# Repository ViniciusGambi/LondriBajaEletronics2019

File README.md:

# LondriBajaEletronics2019

> Este repositório conta um pouco a jornada da evolução do subsistema de elétrica da equipe LondriBaja entre novembro de 2018 e março de 2020. Os detalhes de implementação de cada uma das partes do projeto citadas estão sendo adicionadas em repositórios individuais, as quais seus links são citados aqui ao longo desse texto.

## Jornada

Em Agosto de 2018, novatos na equipe, que naquele momento estava sem membros no subsistema de elétrica, topamos o desafio de mesmo sem estar cursando graduação nas áreas afins, estudar o necessário para conseguir levar um sistema de segurança robusto para a competição, que não gerasse alto número de rechecks para a equipe. A competição Regional Sul seria em outubro. Trabalhamos duro aqueles dois meses para isso. Conseguimos finalizar alguns dias antes da competição, e observando as necessidades da equipe para aquele momento, projetamos um simples sistema para aferir níveis baixos de combustível, de fabricação manual, bem simples, mas que funcionava. Conseguimos chegar na competição e o resultado foi 0 rechecks, e conseguimos uma boa nota, embora marinheiros de primeira viagem. O feedback dos juízes e experiências trocadas com as demais equipes nos mostravam que o segredo era começar com pouco, mas fazer bem feito. Isso nos deu ânimo e mostrava que estávamos no caminho certo. 

Iniciamos então uma nova fase. Definimos então algumas metas. O prazo final era a competição Nacional em março de 2020. Colheríamos mais feedbacks dos juízes nas competições Nacional de 2019, em fevereiro, e Regional Sul de novembro de 2020.

- Implementar o primeiro sistema de instrumentação desenvolvido pela equipe
- Otimizar a proteção contra líquidos do então atual sistema de segurança da equipe
- Desenvolver um sensor de baixo custo para aferir o deslocamento da suspensão
- Desenvolver um aplicativo que facilitasse o processo de fazer inspeções de segurança

### A instalação elétrica

Toda a instalação elétrica do veículo foi novamente projetada em busca de reduzir a massa total do sistema, torná-la mais robusta e mais resistente a líquidos, e mais modular em busca de acelerar o processo de manutenção. O chicote foi fabricado  com tubo anti chamas, conectores IP66, prensa-cabos.Foram projetadas caixas vedadas, fabricadas com impressão 3d e borrachas para a proteção contra líquidos dos botões de emergência.

### Sensoriamento

Seguindo o princípio de fazer algo enxuto, simples porém bem feito, para essa primeira versão foi optado por aferir 3 grandezas: RPM do motor, velocidade do veículo e nível de combustível. Os métodos escolhido para RPM foi extrair os pulsos gerados na bobina da vela, para a velocidade foi o posicionamento de um sensor indutivo no eixo da roda para contagem de pulsos, e para o combustível posicionar sensores capacitivos digitais externos ao tanque (visto que a competição proíbe utilizar sensores dentro do tanque). Mais detalhes podem ser vistos nos repositórios individuais (a serem criados).

### Projeto Elétrico e Eletrônico

O diagrama abaixo mostra como ficou organizado o sistema de segurança junto ao sistema eletrônico. 

O sistema eletrônico foi dividido em duas PCB’s, uma ECU, principal, que cuida do do controle das tensões, conecta o microcontrolador, que trabalha os dados, as entradas dos sensores, e expõe os dados para a Serial e outra PCB, que é um display com leds e displays de 7 segmentos que é utilizada como painel. 
O controle das tensões é feito por dois reguladores buck por apresentarem eficiências mais altas. O microcontrolador, um ATMega328p, foi escolhido para garantir o andamento do projeto no futuro da equipe. Como em nossa universidade não temos alunos cursando a área de eletrônica e afins, essa escolha facilita para que o projeto não fique estagnado até que futuros novos membros possam aprender a programar microcontroladores de baixo nível, pelo fato desse microcontrolador poder ser programado com a biblioteca Arduino, que tem uma grande comunidade e é de fácil aprendizagem. E mesmo assim, se adequa aos requisitos do projeto, atendendo as necessidades do projeto. Os esquemáticos e detalhes da implementação podem ser extraídos nos repositório X.

Foram projetadas caixas vedadas, como as do sistema de segurança, para o sistema de instrumentação. Foram desenvolvidas duas versões das caixas de proteção nesse tempo. A primeira foi projetada em forma de gaveta, em busca de fácil manutenção caso necessário, e guardava ambas as duas PCBs. É a implementada no veículo ao fim deste projeto. A segunda versão separa as PCB’s em duas caixas, em busca de maior modularidade, e substitui os conectores que são utilizadas na primeira versão, por sensores automotivos que se conectam diretamente a PCB, para tornar a solução mais automotiva, e retirar os prensa-cabos. Essa versão será fabricada em 2020, mas o projeto já está pronto ao fim deste ciclo. 

### User Interface e Registro de dados

Para exibir os dados aferidos pelo sistema de instrumentação, foi desenhada uma interface para a exibição dos dados. Para o registro de dados para análises, foi desenvolvido um aplicativo Android que faz registro (como um data logger) dos dados expostos na Serial. (link aqui)

### Validação

Todas as grandezas aferidas foram validadas e ajustadas com equipamentos com valores de referência confiáveis. A validação de RPM do motor foi feita por meio de um tacômetro óptico em bancada. Os valores de combustível foram validados em laboratório. Para a velocidade, pela falta de acesso a um equipamento calibrado de referência, desenvolvemos uma aplicação que extrai os dados de velocidade do aplicativo Waze (por ser a fonte mais segura acessível a equipe) por processamento de imagem, e os guarda registrados em função do tempo em uma planilha para a análise e comparação posterior.

### Extra

A partir de uma necessidade do subsistema de suspensão, que precisava de dados de deslocamento da suspensão, verificamos a possibilidade da compra de um sensor para isso. Como o valor escapava ao orçamento, buscamos uma forma de aferir essa grandeza com um sensor de baixo custo. Inicialmente realizamos alguns testes com um acelerômetro MPU6050, entretanto em virtude da baixa precisão do sensor, o acúmulo de erros ao longo do tempo tornava inviável a integral da aceleração para retirar o deslocamento. Desenvolvemos então uma solução melhor, barata, mais robusta, e com grande precisão com impressão 3D, duas barras lineares e um encoder óptico aproveitados de uma impressora velha. Esse projeto pode ser visualizado nesse outro repositório (a ser upado). 

Outro projeto desenvolvido no ano foi um aplicativo para tornar fácil e rápido o processo da inspeção de segurança, possibilitando que a equipe os faça com mais frequência, com o objetivo de ajudar na redução dos rechecks da equipe. O link do repositório desse projeto será adicionado aqui.

### Resultados

Com as implementações feitas, os objetivos citados anteriormente foram atingidos. Ficamos contentes por nossa evolução nesse período. Saímos de uma equipe que não tinha notas de projeto elétrico até então para o 3º melhor projeto eletrônico do Regional Sul 2019 (entre as 31 equipes inscritas) e o 13º (entre as 78 inscritas) no Nacional 2020. Deixaremos aqui também o banner da apresentação final desse projeto no Nacional de Março de 2020.

## Os autores

Cauê Gaffo, Giovani David e Vinicius Gambi abraçaram o subsistema e lideraram esse processo. No meio de 2019, tivemos a chegada dos trainees Ana Gama, Beatriz Yukari e Victor Toshio que muito ajudaram na fabricação e manutenção do projeto, e darão os próximos passos nessa evolução.

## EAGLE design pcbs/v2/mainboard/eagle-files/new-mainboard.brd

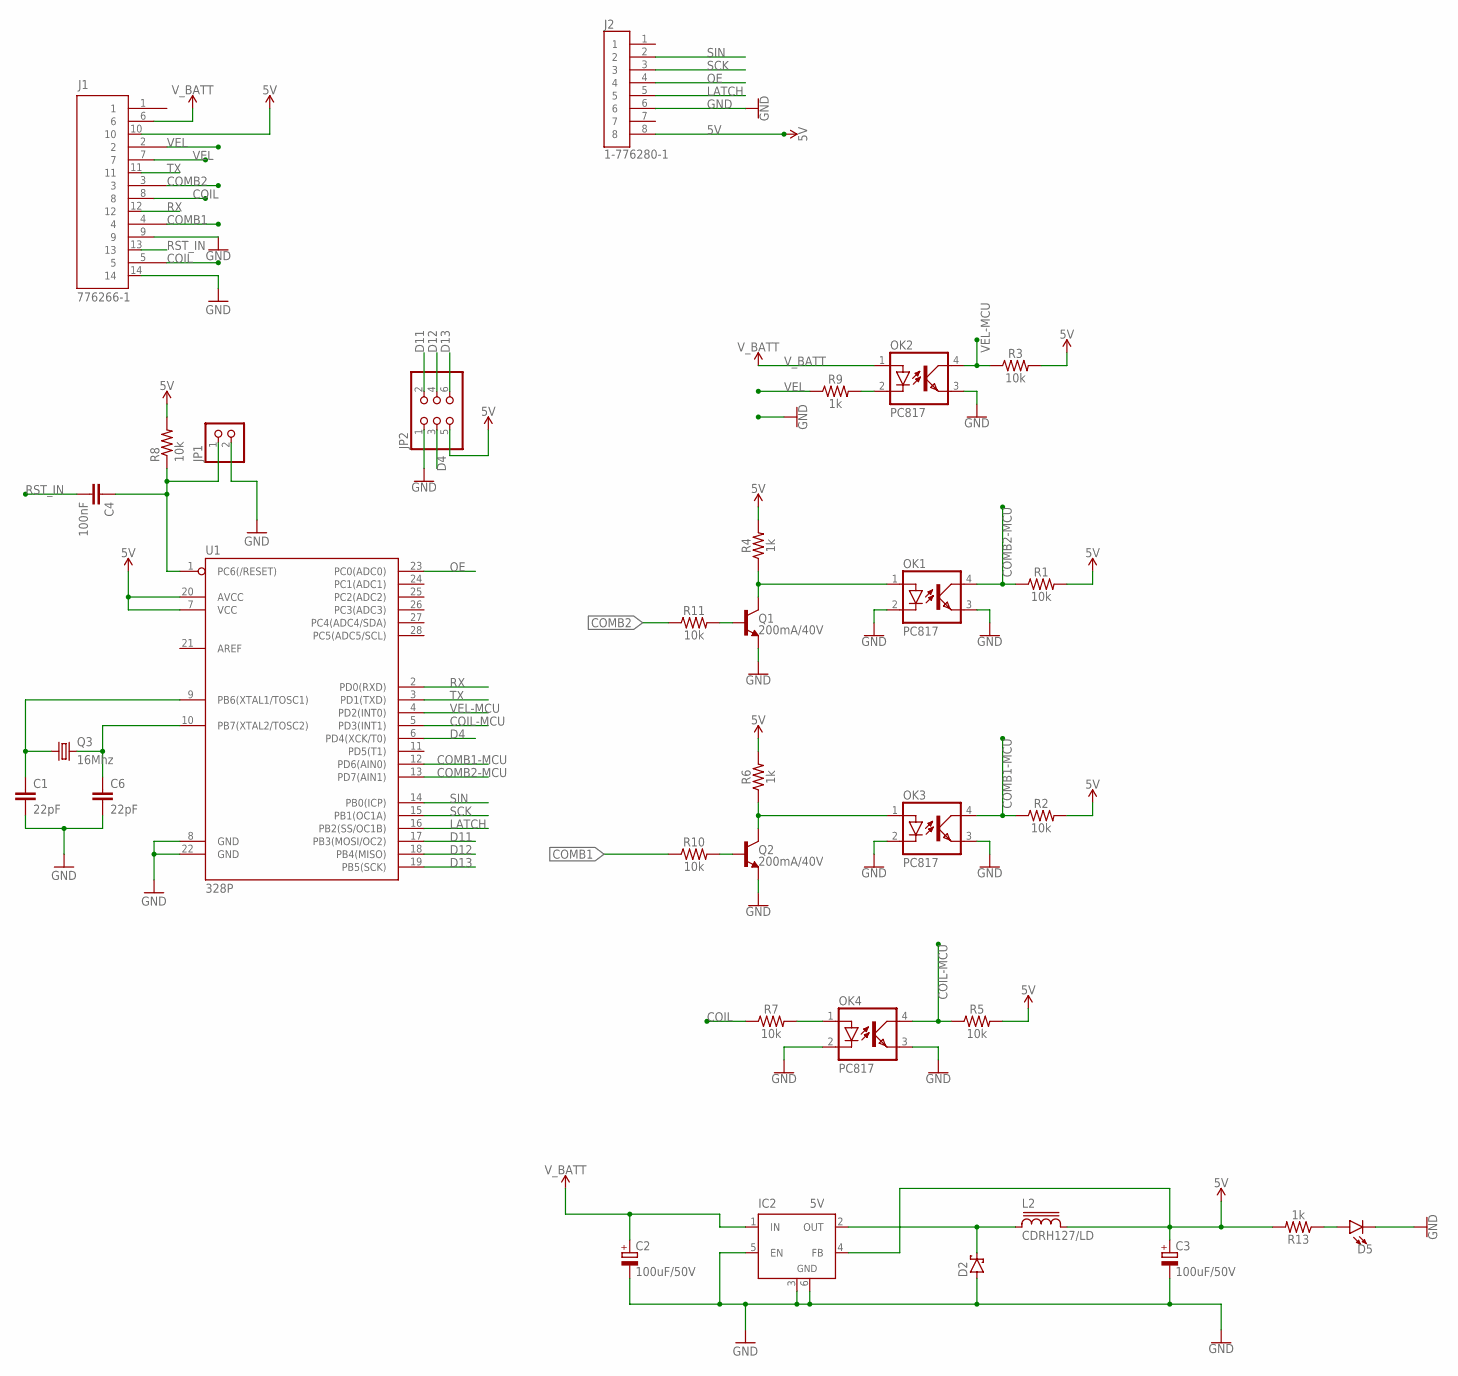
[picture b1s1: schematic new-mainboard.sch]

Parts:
C1, C6: 22pF; CAP-PTH-2.54
C2, C3: 100uF/50V; E3,5-8
C4: 100nF; CAP-PTH-2.54
D2: SCHOTTKY-DIODESMD; SMB
D5: LED3MM; LED_3MM
IC2: 5V; TO263-5
J1: 776266-1; TE_776266-1
J2: 1-776280-1; TE_1-776280-1
JP1: PINHD-1X2; 1X02
JP2: PINHD-2X3; 2X03
L2: CDRH127/LD
OK1, OK2, OK3, OK4: PC817; DIL04
Q1, Q2: 200mA/40V; TO-92
Q3: 16Mhz; HC49U-V
R1, R2, R3, R5, R7, R8, R10, R11: 10k; AXIAL-0.3
R4, R6, R9, R13: 1k; AXIAL-0.3
U1: 328P; DIP28

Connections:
5V: C3.+, IC2.4 (FB), J1.10, J2.8, JP2.5, L2.2, R1.P$2 (2), R2.P$2 (2), R3.P$2 (2), R4.P$2 (2), R5.P$2 (2), R6.P$2 (2), R8.P$2 (2), R13.P$2 (2), U1.7 (VCC), U1.20 (AVCC)
COIL: J1.5, J1.8, R7.P$1 (1)
COIL-MCU: OK4.4 (COL), R5.P$1 (1), U1.5 (PD3(INT1))
COMB1: J1.4, R10.P$1 (1)
COMB1-MCU: OK3.4 (COL), R2.P$1 (1), U1.12 (PD6(AIN0))
COMB2: J1.3, R11.P$1 (1)
COMB2-MCU: OK1.4 (COL), R1.P$1 (1), U1.13 (PD7(AIN1))
D4: JP2.3, U1.6 (PD4(XCK/T0))
D11: JP2.2, U1.17 (PB3(MOSI/OC2))
D12: JP2.4, U1.18 (PB4(MISO))
D13: JP2.6, U1.19 (PB5(SCK))
GND: C1.2, C2.-, C3.-, C6.2, D2.A, D5.K (C), IC2.3 (GND), IC2.5 (EN), IC2.6 (GND), J1.9, J1.14, J2.6, JP1.2, JP2.1, OK1.2 (C), OK1.3 (EMIT), OK2.3 (EMIT), OK3.2 (C), OK3.3 (EMIT), OK4.2 (C), OK4.3 (EMIT), Q1.1 (E), Q2.1 (E), U1.8 (GND), U1.22 (GND)
LATCH: J2.5, U1.16 (PB2(SS/OC1B))
unnamed: OK4.1 (A), R7.P$2 (2)
unnamed: OK2.2 (C), R9.P$2 (2)
unnamed: OK1.1 (A), Q1.3 (C), R4.P$1 (1)
unnamed: OK3.1 (A), Q2.3 (C), R6.P$1 (1)
unnamed: C1.1, Q3.1, U1.9 (PB6(XTAL1/TOSC1))
unnamed: C6.1, Q3.2, U1.10 (PB7(XTAL2/TOSC2))
unnamed: Q2.2 (B), R10.P$2 (2)
unnamed: D5.A, R13.P$1 (1)
unnamed: Q1.2 (B), R11.P$2 (2)
OE: J2.4, U1.23 (PC0(ADC0))
OUT: D2.C, IC2.2 (OUT), L2.1
RST: C4.1, JP1.1, R8.P$1 (1), U1.1 (PC6(/RESET))
RST_IN: C4.2, J1.13
RX: J1.12, U1.2 (PD0(RXD))
SCK: J2.3, U1.15 (PB1(OC1A))
SIN: J2.2, U1.14 (PB0(ICP))
TX: J1.11, U1.3 (PD1(TXD))
VEL: J1.2, J1.7, R9.P$1 (1)
VEL-MCU: OK2.4 (COL), R3.P$1 (1), U1.4 (PD2(INT0))
V_BATT: C2.+, IC2.1 (IN), J1.6, OK2.1 (A)

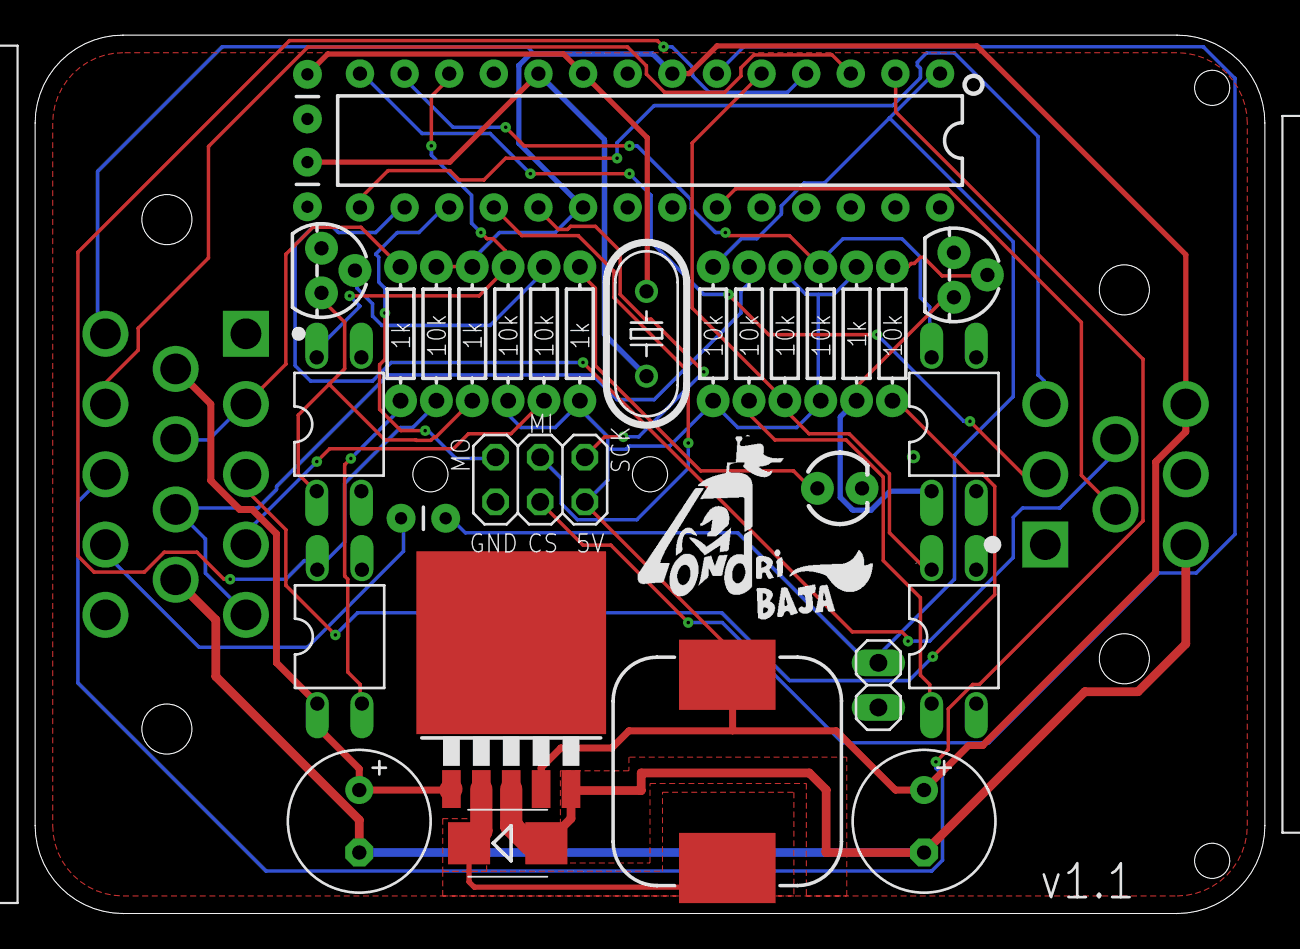
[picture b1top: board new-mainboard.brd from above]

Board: 2 copper layers, 70.0 x 50.0 mm, 33 parts (0 on the bottom side), 33 nets.

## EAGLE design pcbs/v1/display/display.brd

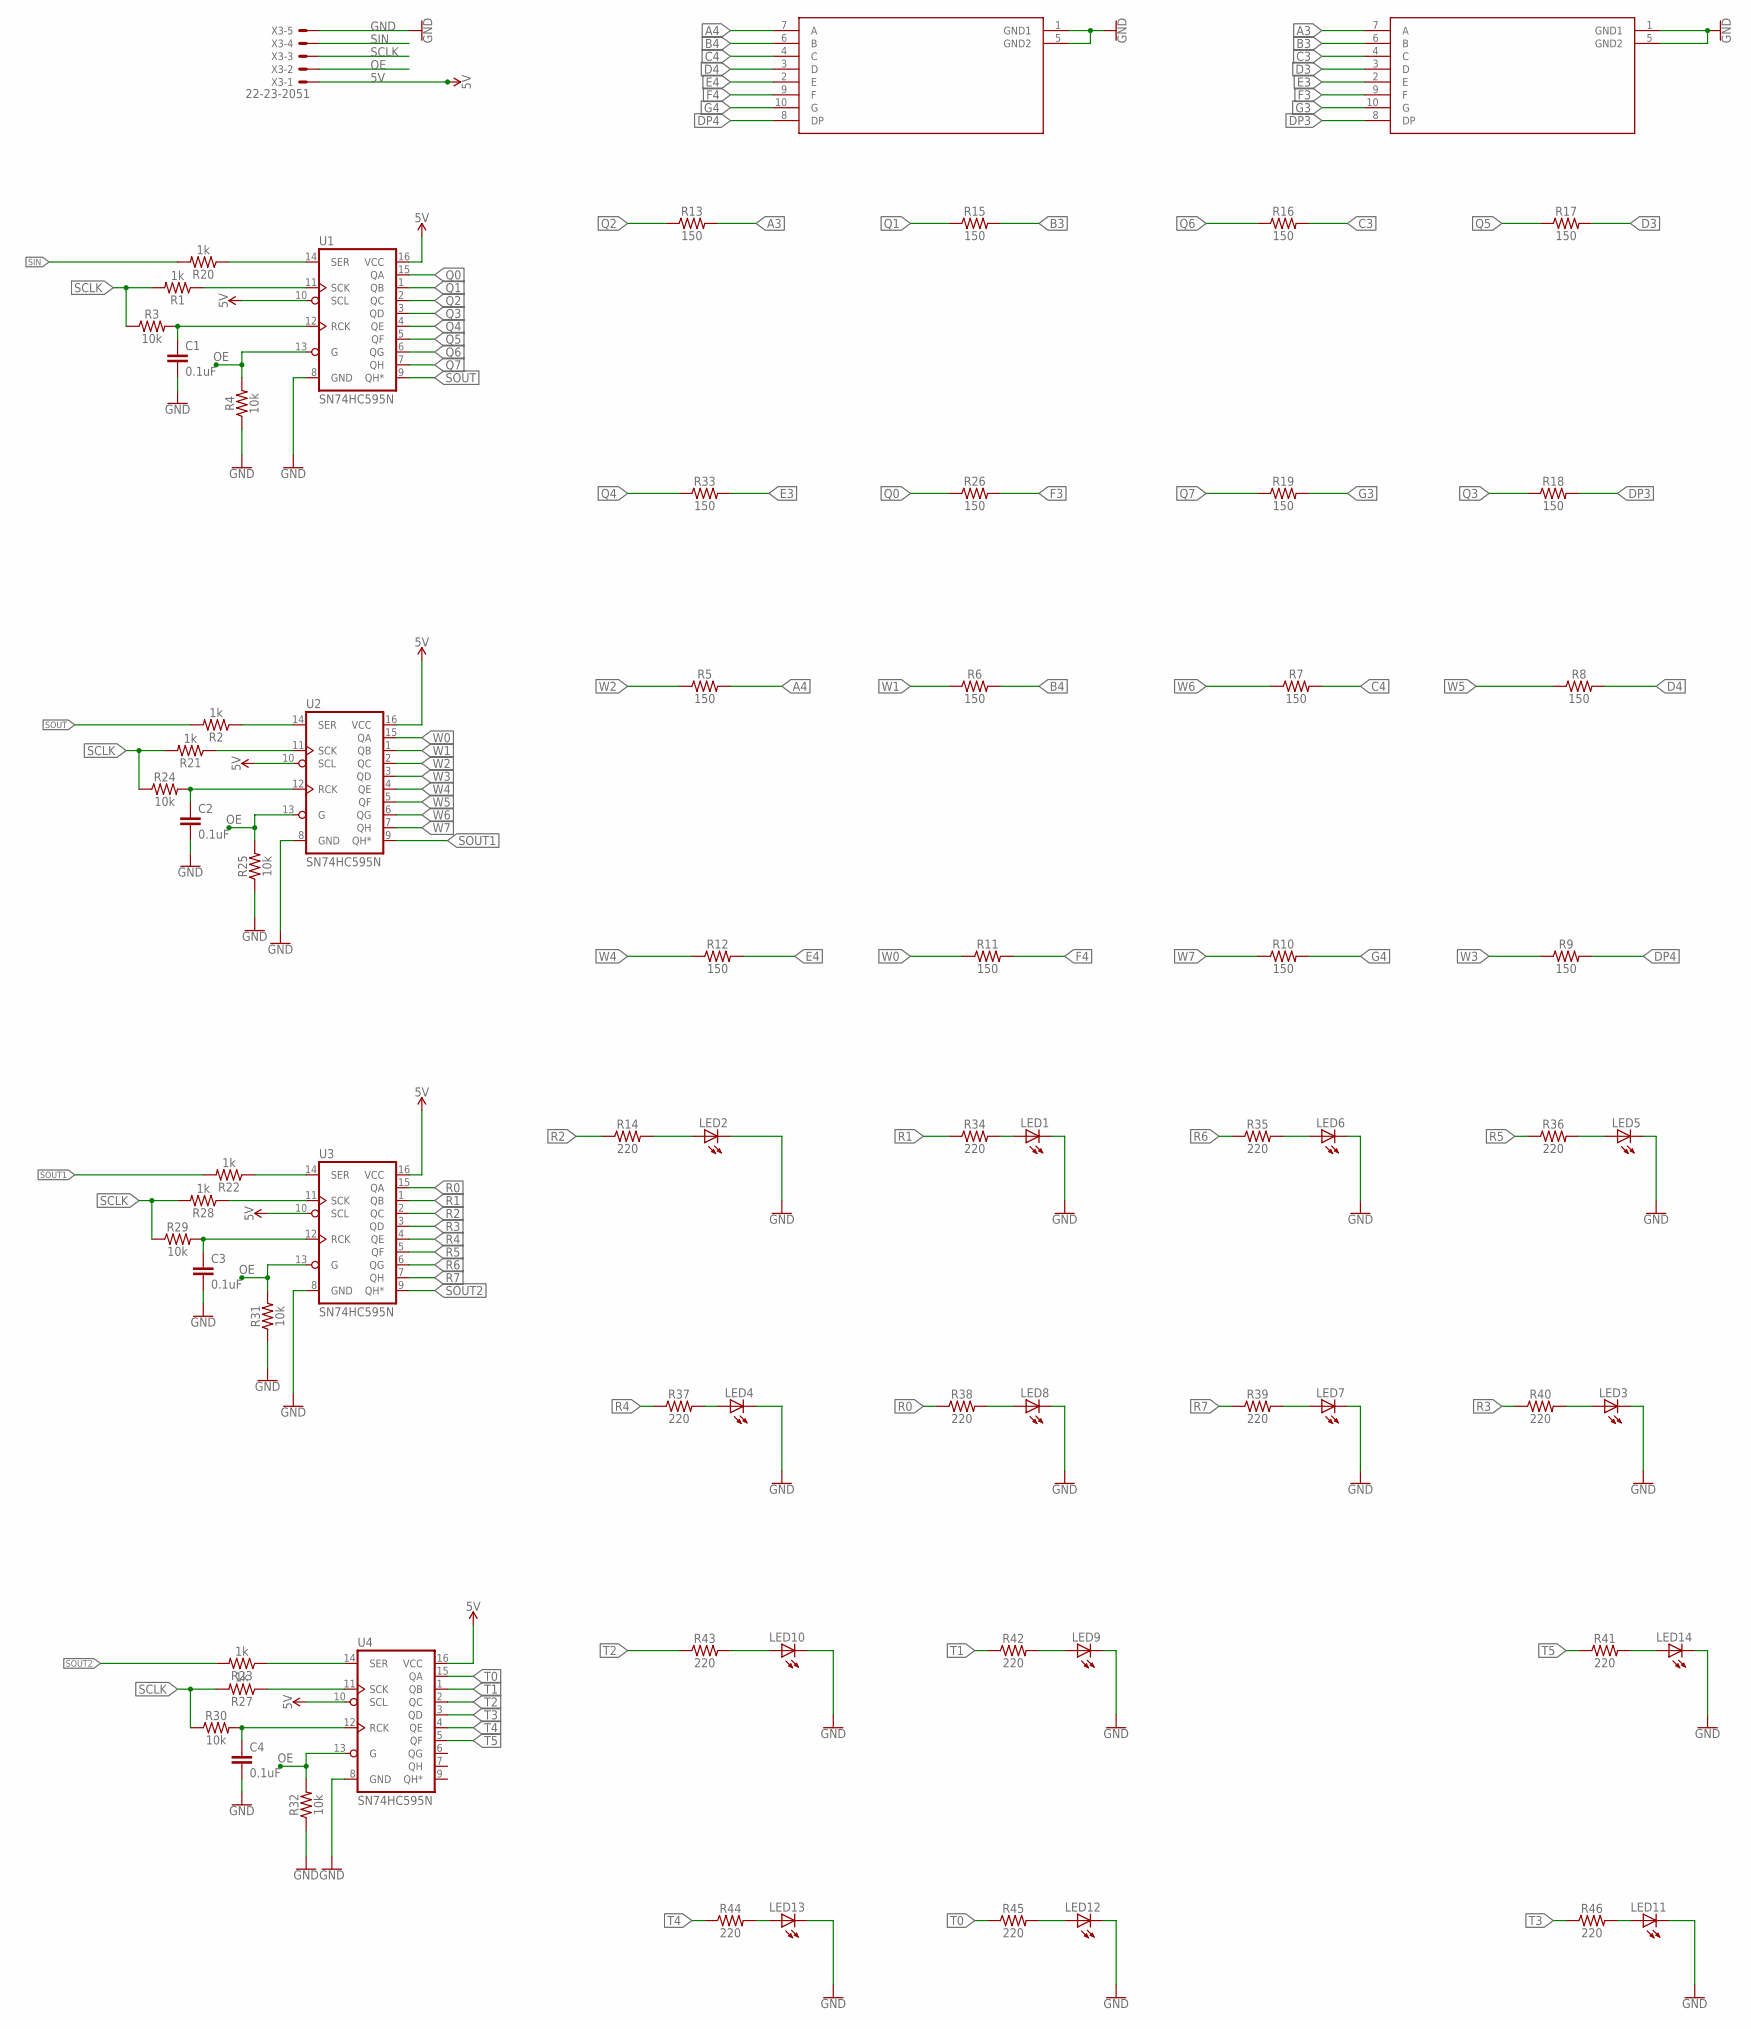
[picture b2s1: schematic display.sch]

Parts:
C1, C2, C3, C4: 0.1uF; CAP-PTH-2.54
LED1, LED2, LED3, LED4, LED5, LED6, LED7, LED8, LED9, LED10, LED11, LED12, LED13, LED14: LED5MM
R1, R2, R20, R21, R22, R23, R27, R28: 1k; AXIAL-0.3
R3, R4, R24, R25, R29, R30, R31, R32: 10k; AXIAL-0.3
R5, R6, R7, R8, R9, R10, R11, R12, R13, R15, R16, R17, R18, R19, R26, R33: 150; AXIAL-0.3
R14, R34, R35, R36, R37, R38, R39, R40, R41, R42, R43, R44, R45, R46: 220; AXIAL-0.3
U1, U2, U3, U4: SN74HC595N; DIP16
U$1, U$2: DISPLAY1.2; 1.2INCH
X3: 22-23-2051

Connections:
5V: U1.10 (SCL), U1.16 (VCC), U2.10 (SCL), U2.16 (VCC), U3.10 (SCL), U3.16 (VCC), U4.10 (SCL), U4.16 (VCC), X3.1
A3: R13.P$2 (2), U$1.7 (A)
A4: R5.P$2 (2), U$2.7 (A)
B3: R15.P$2 (2), U$1.6 (B)
B4: R6.P$2 (2), U$2.6 (B)
C3: R16.P$2 (2), U$1.4 (C)
C4: R7.P$2 (2), U$2.4 (C)
D3: R17.P$2 (2), U$1.3 (D)
D4: R8.P$2 (2), U$2.3 (D)
DP3: R18.P$2 (2), U$1.8 (DP)
DP4: R9.P$2 (2), U$2.8 (DP)
E3: R33.P$2 (2), U$1.2 (E)
E4: R12.P$2 (2), U$2.2 (E)
F3: R26.P$2 (2), U$1.9 (F)
F4: R11.P$2 (2), U$2.9 (F)
G3: R19.P$2 (2), U$1.10 (G)
G4: R10.P$2 (2), U$2.10 (G)
GND: C1.2, C2.2, C3.2, C4.2, LED1.K (C), LED2.K (C), LED3.K (C), LED4.K (C), LED5.K (C), LED6.K (C), LED7.K (C), LED8.K (C), LED9.K (C), LED10.K (C), LED11.K (C), LED12.K (C), LED13.K (C), LED14.K (C), R4.P$1 (1), R25.P$1 (1), R31.P$1 (1), R32.P$1 (1), U1.8 (GND), U2.8 (GND), U3.8 (GND), U4.8 (GND), U$1.1 (GND1), U$1.5 (GND2), U$2.1 (GND1), U$2.5 (GND2), X3.5
unnamed: R20.P$1 (1), U1.14 (SER)
unnamed: R1.P$1 (1), U1.11 (SCK)
unnamed: C1.1, R3.P$2 (2), U1.12 (RCK)
unnamed: R2.P$1 (1), U2.14 (SER)
unnamed: R21.P$1 (1), U2.11 (SCK)
unnamed: C2.1, R24.P$2 (2), U2.12 (RCK)
unnamed: LED4.A, R37.P$2 (2)
unnamed: LED8.A, R38.P$2 (2)
unnamed: LED7.A, R39.P$2 (2)
unnamed: LED3.A, R40.P$2 (2)
unnamed: LED5.A, R36.P$2 (2)
unnamed: LED6.A, R35.P$2 (2)
unnamed: LED1.A, R34.P$2 (2)
unnamed: LED2.A, R14.P$2 (2)
unnamed: LED10.A, R43.P$2 (2)
unnamed: R22.P$1 (1), U3.14 (SER)
unnamed: R28.P$1 (1), U3.11 (SCK)
unnamed: C3.1, R29.P$2 (2), U3.12 (RCK)
unnamed: LED9.A, R42.P$2 (2)
unnamed: LED11.A, R46.P$2 (2)
unnamed: LED14.A, R41.P$2 (2)
unnamed: LED12.A, R45.P$2 (2)
unnamed: R23.P$1 (1), U4.14 (SER)
unnamed: R27.P$1 (1), U4.11 (SCK)
unnamed: C4.1, R30.P$2 (2), U4.12 (RCK)
unnamed: LED13.A, R44.P$2 (2)
OE: R4.P$2 (2), R25.P$2 (2), R31.P$2 (2), R32.P$2 (2), U1.13 (G), U2.13 (G), U3.13 (G), U4.13 (G), X3.2
Q0: R26.P$1 (1), U1.15 (QA)
Q1: R15.P$1 (1), U1.1 (QB)
Q2: R13.P$1 (1), U1.2 (QC)
Q3: R18.P$1 (1), U1.3 (QD)
Q4: R33.P$1 (1), U1.4 (QE)
Q5: R17.P$1 (1), U1.5 (QF)
Q6: R16.P$1 (1), U1.6 (QG)
Q7: R19.P$1 (1), U1.7 (QH)
R0: R38.P$1 (1), U3.15 (QA)
R1: R34.P$1 (1), U3.1 (QB)
R2: R14.P$1 (1), U3.2 (QC)
R3: R40.P$1 (1), U3.3 (QD)
R4: R37.P$1 (1), U3.4 (QE)
R5: R36.P$1 (1), U3.5 (QF)
R6: R35.P$1 (1), U3.6 (QG)
R7: R39.P$1 (1), U3.7 (QH)
SCLK: R1.P$2 (2), R3.P$1 (1), R21.P$2 (2), R24.P$1 (1), R27.P$2 (2), R28.P$2 (2), R29.P$1 (1), R30.P$1 (1), X3.3
SIN: R20.P$2 (2), X3.4
SOUT: R2.P$2 (2), U1.9 (QH*)
SOUT1: R22.P$2 (2), U2.9 (QH*)
SOUT2: R23.P$2 (2), U3.9 (QH*)
T0: R45.P$1 (1), U4.15 (QA)
T1: R42.P$1 (1), U4.1 (QB)
T2: R43.P$1 (1), U4.2 (QC)
T3: R46.P$1 (1), U4.3 (QD)
T4: R44.P$1 (1), U4.4 (QE)
T5: R41.P$1 (1), U4.5 (QF)
W0: R11.P$1 (1), U2.15 (QA)
W1: R6.P$1 (1), U2.1 (QB)
W2: R5.P$1 (1), U2.2 (QC)
W3: R9.P$1 (1), U2.3 (QD)
W4: R12.P$1 (1), U2.4 (QE)
W5: R8.P$1 (1), U2.5 (QF)
W6: R7.P$1 (1), U2.6 (QG)
W7: R10.P$1 (1), U2.7 (QH)

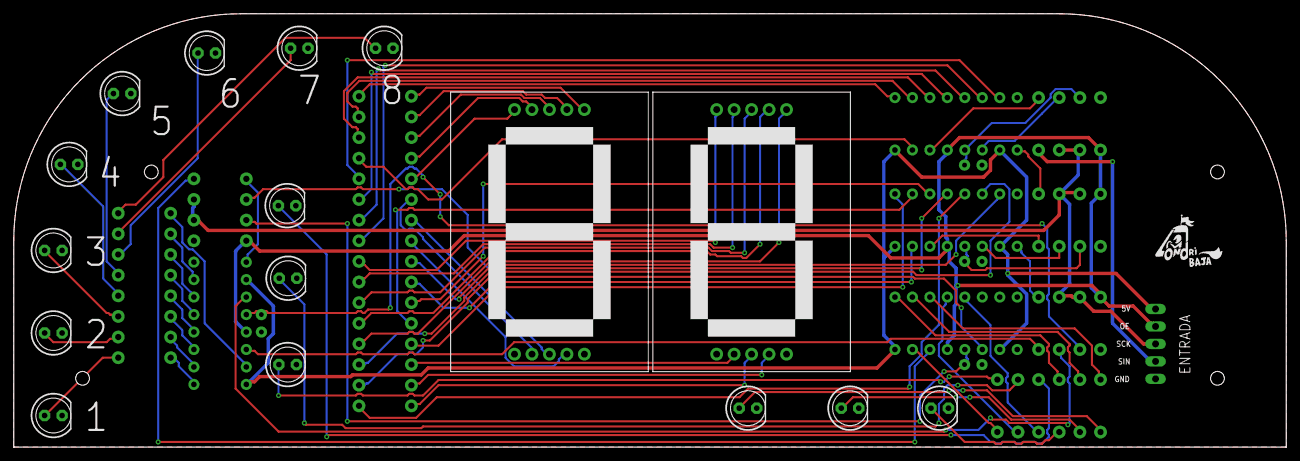
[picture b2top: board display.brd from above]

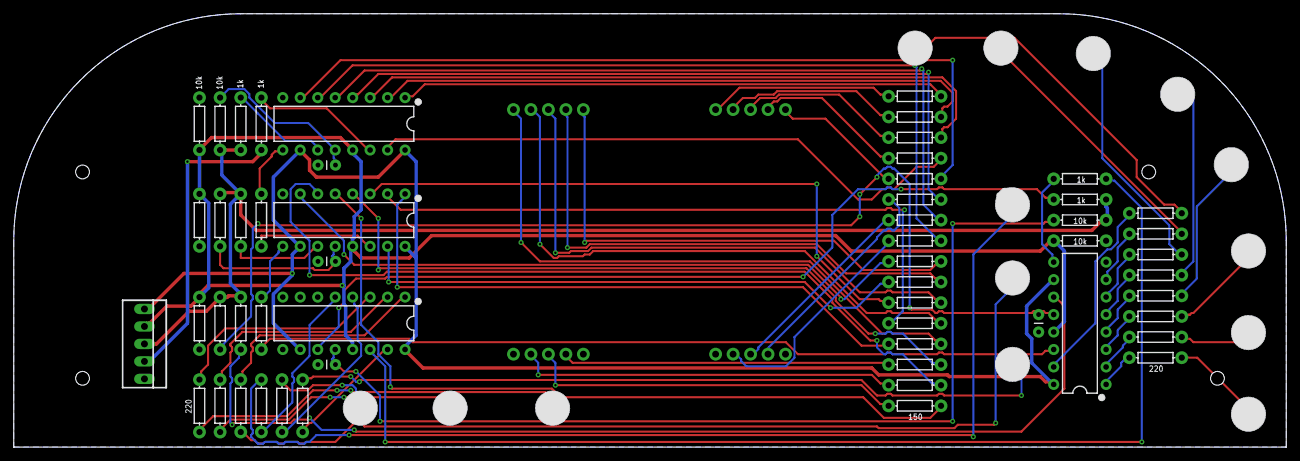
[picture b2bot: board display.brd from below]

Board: 2 copper layers, 185.0 x 63.0 mm, 71 parts (55 on the bottom side), 80 nets.

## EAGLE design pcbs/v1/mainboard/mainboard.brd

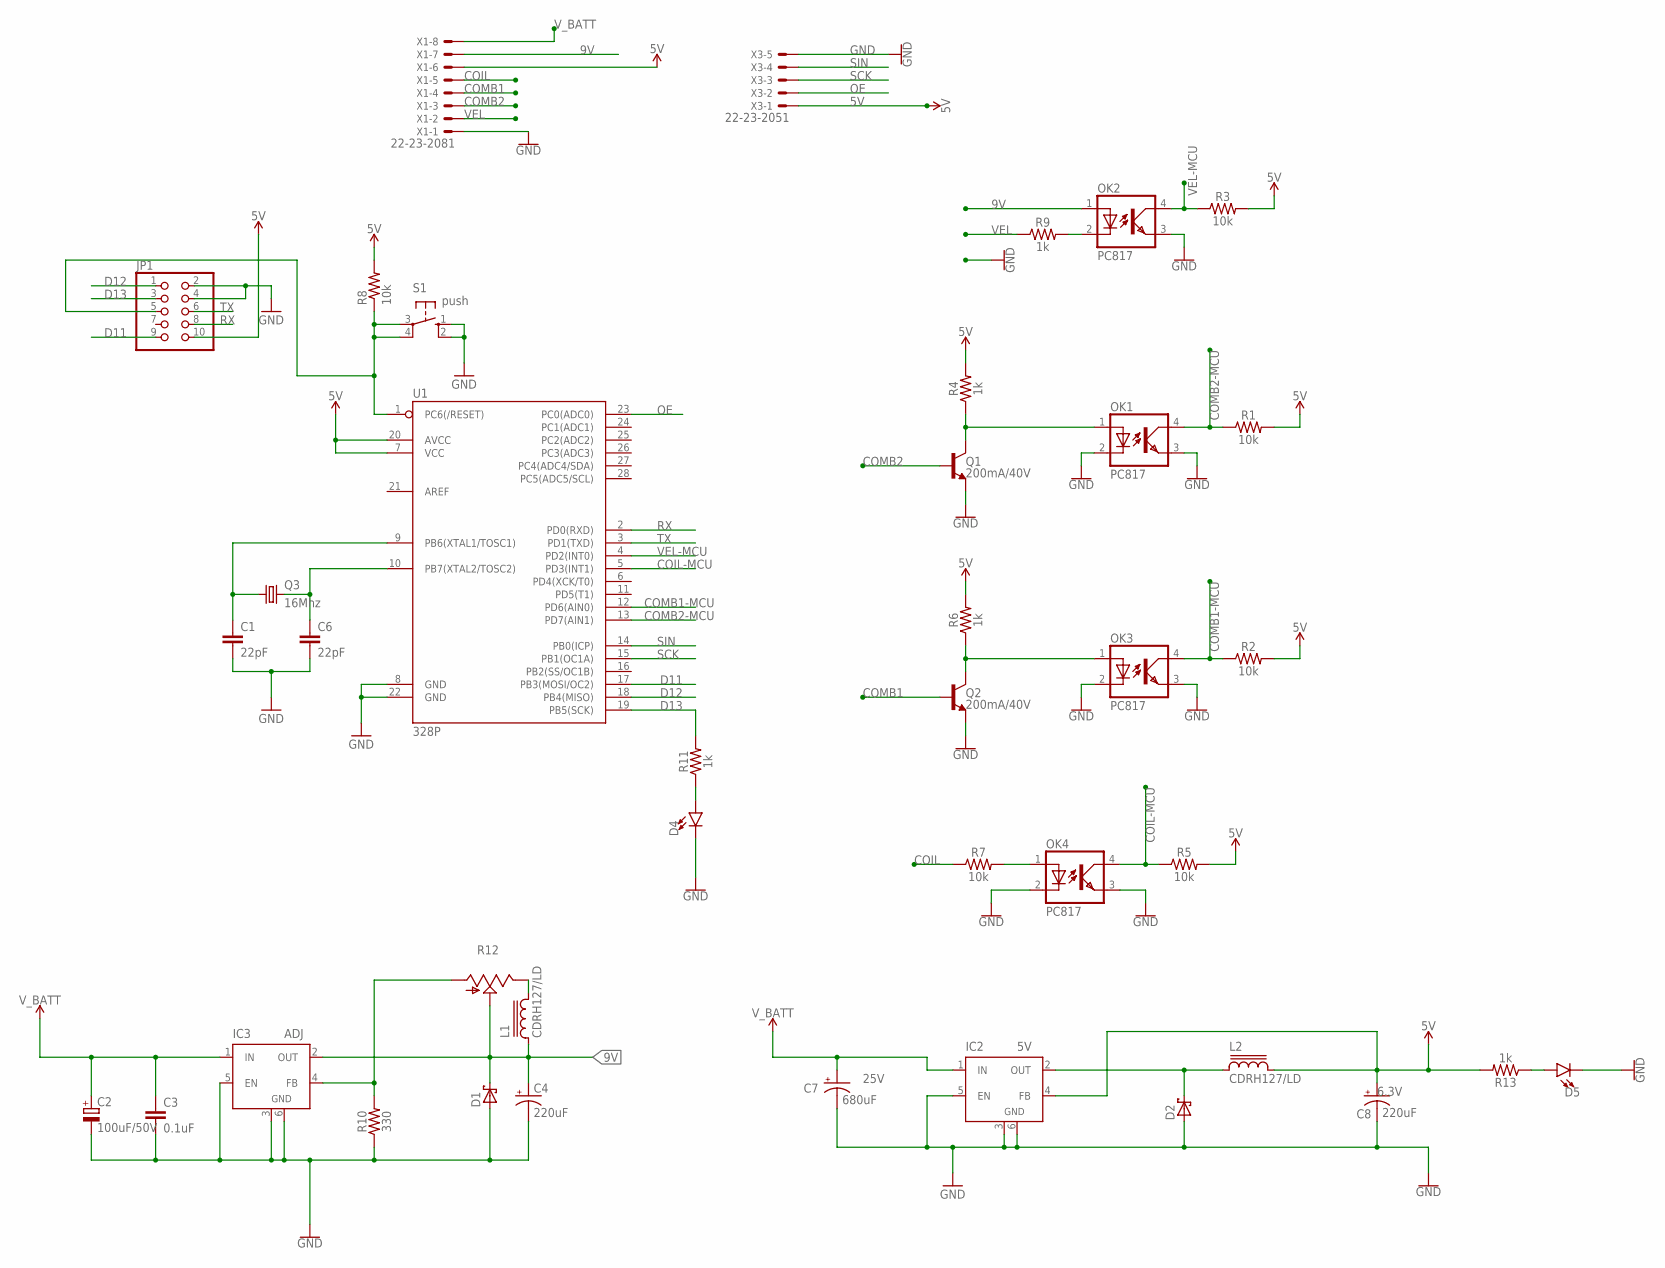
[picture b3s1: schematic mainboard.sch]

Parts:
C1, C6: 22pF; CAP-PTH-2.54
C2: 100uF/50V; E3,5-8
C3: 0.1uF; 0603
C4: 220uF; UD-6,3X5,8_NICHICON
C7: 680uF; E5-10,5; VOLTAGE 25V
C8: 220uF; UD-6,3X5,8_NICHICON; VOLTAGE 6.3V
D1, D2: SCHOTTKY-DIODESMD; SMB
D4, D5: LED3MM; LED_3MM
IC2: 5V; TO263-5
IC3: ADJ; TO263-5
JP1: PINHD-2X5; 2X05
L1, L2: CDRH127/LD
OK1, OK2, OK3, OK4: PC817; DIL04
Q1, Q2: 200mA/40V; TO-92
Q3: 16Mhz; HC49U-V
R1, R2, R3, R5, R7, R8: 10k; AXIAL-0.3
R4, R6, R9, R11, R13: 1k; AXIAL-0.3
R10: 330; AXIAL-0.3
R12: TRIM_US-S64W; S64W
S1: push; B3F-10XX
U1: 328P; DIP28
X1: 22-23-2081
X3: 22-23-2051

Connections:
5V: C8.+, IC2.4 (FB), JP1.10, L2.2, R1.P$2 (2), R2.P$2 (2), R3.P$2 (2), R4.P$2 (2), R5.P$2 (2), R6.P$2 (2), R8.P$2 (2), R13.P$2 (2), U1.7 (VCC), U1.20 (AVCC), X1.6, X3.1
9V: C4.+, D1.C, IC3.2 (OUT), L1.1, OK2.1 (A), R12.S, X1.7
COIL: R7.P$1 (1), X1.5
COIL-MCU: OK4.4 (COL), R5.P$1 (1), U1.5 (PD3(INT1))
COMB1: Q2.2 (B), X1.4
COMB1-MCU: OK3.4 (COL), R2.P$1 (1), U1.12 (PD6(AIN0))
COMB2: Q1.2 (B), X1.3
COMB2-MCU: OK1.4 (COL), R1.P$1 (1), U1.13 (PD7(AIN1))
D11: JP1.9, U1.17 (PB3(MOSI/OC2))
D12: JP1.1, U1.18 (PB4(MISO))
D13: JP1.3, R11.P$2 (2), U1.19 (PB5(SCK))
GND: C1.2, C2.-, C3.2, C4.-, C6.2, C7.-, C8.-, D1.A, D2.A, D4.K (C), D5.K (C), IC2.3 (GND), IC2.5 (EN), IC2.6 (GND), IC3.3 (GND), IC3.5 (EN), IC3.6 (GND), JP1.2, JP1.4, OK1.2 (C), OK1.3 (EMIT), OK2.3 (EMIT), OK3.2 (C), OK3.3 (EMIT), OK4.2 (C), OK4.3 (EMIT), Q1.1 (E), Q2.1 (E), R10.P$1 (1), S1.1 (S), S1.2 (S1), U1.8 (GND), U1.22 (GND), X1.1, X3.5
unnamed: OK4.1 (A), R7.P$2 (2)
unnamed: OK2.2 (C), R9.P$2 (2)
unnamed: OK1.1 (A), Q1.3 (C), R4.P$1 (1)
unnamed: OK3.1 (A), Q2.3 (C), R6.P$1 (1)
unnamed: C1.1, Q3.1, U1.9 (PB6(XTAL1/TOSC1))
unnamed: C6.1, Q3.2, U1.10 (PB7(XTAL2/TOSC2))
unnamed: JP1.5, R8.P$1 (1), S1.3, S1.4 (P1), U1.1 (PC6(/RESET))
unnamed: D5.A, R13.P$1 (1)
unnamed: L1.2, R12.E
unnamed: IC3.4 (FB), R10.P$2 (2), R12.A
unnamed: D4.A, R11.P$1 (1)
OE: U1.23 (PC0(ADC0)), X3.2
OUT: D2.C, IC2.2 (OUT), L2.1
RX: JP1.8, U1.2 (PD0(RXD))
SCK: U1.15 (PB1(OC1A)), X3.3
SIN: U1.14 (PB0(ICP)), X3.4
TX: JP1.6, U1.3 (PD1(TXD))
VEL: R9.P$1 (1), X1.2
VEL-MCU: OK2.4 (COL), R3.P$1 (1), U1.4 (PD2(INT0))
V_BATT: C2.+, C3.1, C7.+, IC2.1 (IN), IC3.1 (IN), X1.8

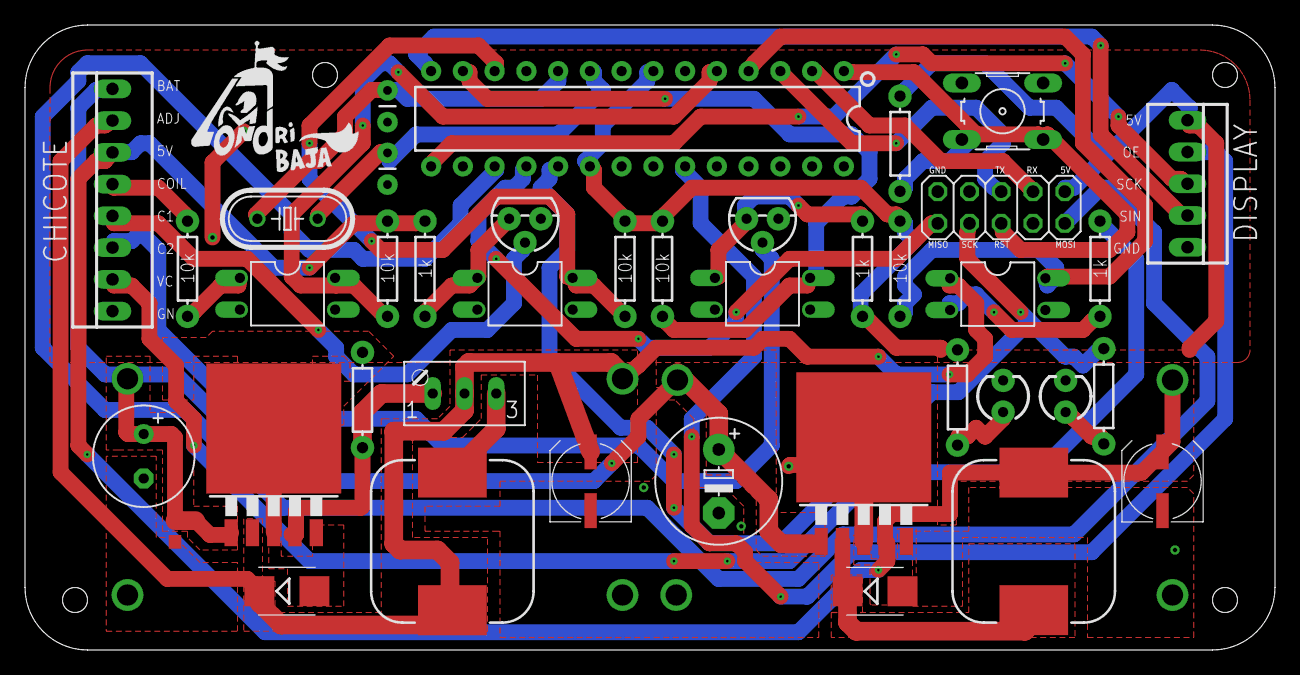
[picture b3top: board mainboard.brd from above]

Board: 2 copper layers, 100.0 x 50.0 mm, 40 parts (0 on the bottom side), 32 nets.

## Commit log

2020-11-11 first readme commit
2020-11-11 eletric-eletronic image added
2020-11-11 image url correction
2020-11-11 pt-br image alteration
2020-11-11 Bullet List
2020-11-12 some images added
2020-11-13 Results added
2020-11-13 authors added
2020-11-13 some files added
2020-11-13 banner added
2020-11-13 readme updated
2020-11-13 pcbs readme
2020-11-13 size update
2020-11-13 eagle-files folder added
2020-11-13 some folder updates

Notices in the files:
parts and their libraries:
SparkFun-Resistors: Licensing: Creative Commons ShareAlike 4.0 International - https://creativecommons.org/licenses/by-sa/4.0
inductor-sumida: Copyright (C) 2008, Bob Starr
